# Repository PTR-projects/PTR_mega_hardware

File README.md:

# KPPTR-hardware

Welcome to the KPPTR-hardware repository! This repository contains the design files for the hardware components used in the KPPTR project. The design files have been created using KiCad 6.0, a powerful open-source electronics design automation suite.

## Project Overview

The design files in this repository correspond to the hardware components that make up the KPPTR project, which enhances the capabilities of DIY amateur rockets and high-altitude balloons. The design files have been crafted using KiCad 6.0, a popular and user-friendly tool for creating electronic schematics and PCB layouts. Both hardware and sofware were developed by PTR member!

## Design Files

The repository includes design files for the various hardware components used in the KPPTR project, including:

- **Schematics**: Detailed electronic schematics that illustrate the connections and components used in the design.
- **PCB Layouts**: PCB layout designs that define the placement and routing of components on the printed circuit board.
- **Libraries**: Custom component libraries and footprints used in the project.

## Getting Started

To access and work with the design files, follow these steps:

1. Clone the repository to your local machine.
2. Install [KiCad 9.X](https://www.kicad.org/download/) if you haven't already.
3. Open the KiCad project files (`.pro` files) in the appropriate subdirectories to access the schematics and PCB layouts.

Feel free to explore the design files and customize them to suit your specific needs. If you make any improvements or modifications to the hardware designs, consider contributing back to the repository to help the community.

## Contributors

- [bartekM](https://gitlab.com/space.tech)
- [https://gitlab.com/andrewziebinski](https://gitlab.com/andrewziebinski)
- [https://gitlab.com/Bdabrowsky](https://gitlab.com/Bdabrowsky)
- [https://gitlab.com/krecik1](https://gitlab.com/krecik1)
- [https://gitlab.com/US_air_force](https://gitlab.com/US_air_force)
- [https://gitlab.com/karmelek96](https://gitlab.com/karmelek96)
- and many others!

## License

This project is licensed under the [MIT License](LICENSE). You can freely use, modify, and distribute the code in accordance with the terms of the license.

Unless required by applicable law or agreed to in writing, this
software is distributed on an "AS IS" BASIS, WITHOUT WARRANTIES OR
CONDITIONS OF ANY KIND, either express or implied.

Thank you for your interest in KPPTR-firmware! If you have any questions or feedback, please don't hesitate to reach out to us. Happy coding and safe flights!

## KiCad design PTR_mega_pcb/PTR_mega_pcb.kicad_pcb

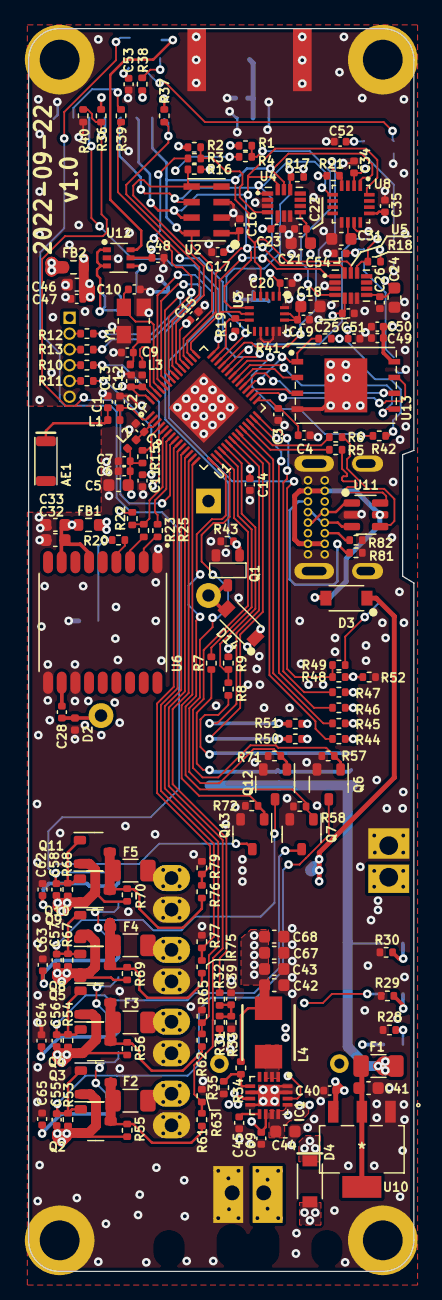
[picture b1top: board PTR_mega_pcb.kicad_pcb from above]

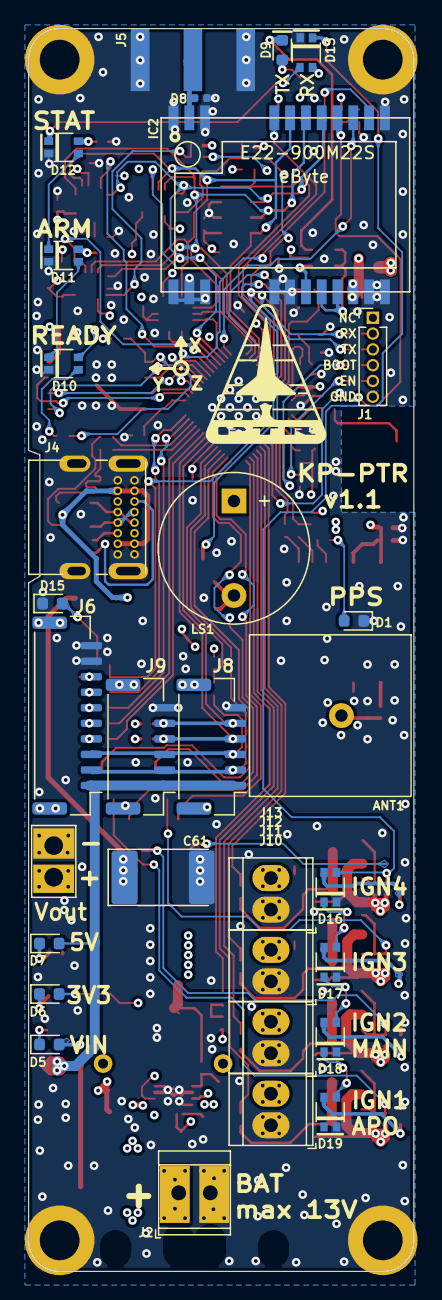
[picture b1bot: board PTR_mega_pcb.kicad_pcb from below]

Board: 4 copper layers, 31.0 x 100.0 mm, 207 parts (32 on the bottom side), 123 nets.

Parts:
AE1: Antenna_Chip; AMCA31-2R450G-S1F-T3
ANT1: APAE1575R1340ABDD6-T; APAE1575 13x13x4mm GPS Patch Antenna
C1: 3.3pF; C_0402_1005Metric
C2: 4.7pF; C_0402_1005Metric
C3, C7, C8, C14, C15, C47, C48: 100n; C_0402_1005Metric
C4, C17, C34, C50, C55, C56, C57, C58: 1uF; C_0402_1005Metric
C5: 10u; C_0603_1608Metric
C6, C11, C13: 1u; C_0402_1005Metric
C9, C10: 12p; C_0402_1005Metric
C12, C39: 10n; C_0402_1005Metric
C16, C19, C20, C22, C23, C25, C26, C35, C49, C51, C52, C53, C54, C62, C63, C64, C65: 100nF; C_0402_1005Metric
C18, C21, C24, C31, C32, C33, C46: 10uF; C_0603_1608Metric
C28: 56pF; C_0402_1005Metric
C40, C69: 100n 50V; C_0402_1005Metric
C41, C42, C43, C67, C68: 10uF 6V3; C_0603_1608Metric
C44: 10uF 16V; C_0603_1608Metric
C45: 470pF; C_0402_1005Metric
C61: 2200uF 16V; CP_EIA-7343-31_Kemet-D
D1, D9: BLUE; LED_0603_1608Metric
D2: DNP; D_0402_1005Metric
D3, D4: D_Schottky; D_SOD-123
D5, D6, D7, D15: GREEN; LED_0603_1608Metric
D8: TBD; D_0402_1005Metric
D10, D11, D12, D13, D16, D17, D18, D19: WS2812B-2020
D14: 1N4148; D_SOD-123
F1, F2, F3, F4, F5: 500mA; Fuse_1206_3216Metric
FB1, FB2: GZ1608D601TF; R_0603_1608Metric
H1, H2, H3, H4: M3; MountingHole_3.2mm_M3_DIN965_Pad
IC1: TPS62140RGTR; QFN50P300X300X100-17N-D
IC2: E22-400M22S; E22-900M22S
J1: ESP32_PROG_CON; PinHeader_1x06_P1.27mm_Vertical
J2, J10, J11, J12, J13: Conn_01x02; TerminalBlock_TE_282834-2_1x02_P2.54mm_Horizontal
J4: USB_C_Receptacle_USB2.0; USB_C_213716
J5: u.fl; SMA_Amphenol_132289_EdgeMount
J6: Conn_01x10_Male; JST_GH_BM10B-GHS-TBT_1x10-1MP_P1.25mm_Vertical
J7: Conn_01x02_Male; TerminalBlock_TE_282834-2_1x02_P2.54mm_Horizontal
J8, J9: Conn_01x06_Male; JST_GH_BM06B-GHS-TBT_1x06-1MP_P1.25mm_Vertical
L1: 1.8nH; L_0402_1005Metric
L2: 3.9nH; L_0402_1005Metric
L3: 24nH; L_0402_1005Metric
L4: MWSA0402S-2R2MT; INDPM4442X200N
LS1: CBT-09427-SMT; Buzzer_12x9.5RM7.6
M1: Reference_frame
Q1, Q6, Q7, Q12, Q13: NMOS_SOT23; SOT-23
Q2, Q3, Q4, Q5, Q8, Q9, Q10, Q11: PMOS_SOT23; SOT-23
R1, R2, R3, R4, R15, R16, R17, R18, R19, R20, R21, R22, R29, R30, R36, R37, R39, R41, R43, R50, R51, R52, R53, R54, R55, R56, R57, R58, R63, R65, R67, R68, R69, R70, R71, R72, R77, R79: 10k; R_0402_1005Metric
R5, R6: 22R; R_0402_1005Metric
R7, R8, R10, R11, R12, R13, R23, R42, R44, R45, R46, R47, R48, R49: 1k; R_0402_1005Metric
R9, R32, R61, R62, R75, R76: 100k; R_0402_1005Metric
R25: 220; R_0402_1005Metric
R28: 22k; R_0402_1005Metric
R31: 100k 1%; R_0402_1005Metric
R33: 10k 1%; R_0402_1005Metric
R34: 470k 1%; R_0402_1005Metric
R35: 150k 1%; R_0402_1005Metric
R38: 2k2; R_0402_1005Metric
R40: DNP; R_0402_1005Metric
R81, R82: 5k1; R_0402_1005Metric
U1: ESP32-S3
U2: MS560702BA03-50; MS5607
U3: H3LIS331; LIS331
U4, U5: LSM6DSO32
U6: L76-L; XCVR_L76-L
U8: MMC5983MA
U10: AZ1117CH-5.0TRG1
U11: USBLC6-2SC6; SOT-23-6
U12: NL27WZU04DBVT1G; SOT-363_SC-70-6
U13: W25Q256; SON127P800X600X80-9N-D
Y1: 7M40000005-40MHz; XTAL_TSX-3225_16.0000MF18X-AC3

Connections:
+3.3VADC: C32.1, C33.1, FB1.2, U6.6 (V_BCKP), U6.8 (VCC)
+3.3VP: C46.1, C47.1, C48.1, FB2.2, IC2.9 (VCC), R36.1, R37.1, R38.1, U12.5 (VCC)
+3V3: C5.1, C6.1, C7.1, C12.1, C13.1, C14.1, C15.1, C16.1, C17.1, C18.1, C19.1, C20.1, C21.1, C22.1, C23.1, C24.1, C25.1, C26.1, C34.1, C35.1, C42.1, C43.1, C49.1, C50.1, C51.1, C52.1, C53.1, C54.1, C62.1, C63.1, C64.1, C65.1, C67.1, C68.1, D6.2 (A), D10.4 (VDD), D11.4 (VDD), D12.4 (VDD), D13.4 (VDD), D14.1 (K), D16.4 (VDD), D17.4 (VDD), D18.4 (VDD), D19.4 (VDD), FB1.1, FB2.1, IC1.7 (FSW), IC1.14 (VOS), J1.1 (3V3), L2.1, L4.2, LS1.1 (+), R1.2, R2.2, R9.2, R15.2, R16.1, R17.1, R18.1, R19.1, R21.1, R22.1, R34.1, R41.1, R50.2, R51.2, U1.20 (VDD3P3_RTC), U1.46 (VDD3P3_CPU), U1.55 (VDDA), U1.56 (VDDA), U2.1 (VDD), U3.1 (VDDIO), U3.14 (VDD), U3.15 (VDDR), U4.5 (VDDIO), U4.8 (VDD), U5.5 (VDDIO), U5.8 (VDD), U8.2 (VDD), U8.13 (VDDIO), U13.8 (VCC)
+5V: D7.2 (A), F1.1, J6.1, J8.1, J9.1
BOOT_PIN: J1.4 (BOOT), R10.2
BUZZER: Q1.1 (G), R43.2, U1.51 (GPIO45)
CHIP_PU: C11.2, R11.1, R15.1, U1.4 (CHIP_PU/RESET)
Earth: C1.2, C2.2, C3.2, C4.2, C5.2, C6.2, C7.2, C8.2, C9.1, C10.2, C11.1, C12.2, C13.2, C14.2, C15.2, C16.2, C17.2, C18.2, C19.2, C20.2, C21.2, C22.2, C23.2, C24.2, C25.2, C26.2, C31.2, C32.2, C33.2, C34.2, C35.2, C39.2, C40.2, C41.2, C42.2, C43.2, C44.2, C45.1, C46.2, C47.2, C48.2, C49.2, C50.2, C51.2, C52.2, C53.2, C54.2, C61.2, C62.2, C63.2, C64.2, C65.2, C67.2, C68.2, C69.2, D1.1 (K), D2.1 (A1), D8.1 (A1), D10.2 (GND), D11.2 (GND), D12.2 (GND), D13.2 (GND), D15.1 (K), D16.2 (GND), D17.2 (GND), D18.2 (GND), D19.2 (GND), H1.1, H2.1, H3.1, H4.1, IC1.6 (AGND), IC1.8 (DEF), IC1.15 (PGND_1), IC1.16 (PGND_2), IC1.17 (EP), IC2.1 (GND), IC2.2 (GND), IC2.3 (GND), IC2.4 (GND), IC2.5 (GND), IC2.10 (GND), IC2.11 (GND), IC2.12 (GND), IC2.20 (GND), IC2.22 (GND), J1.6 (GND), J2.2, J4.A1 (GND), J4.A12 (GND), J4.B1 (GND), J4.B12 (GND), J4.S1 (SHIELD), J5.2 (Ext), J6.9, J6.10, J7.2, J8.6, J9.6, J10.1, J11.1, J12.1, J13.1, Q1.2 (S), Q6.2 (S), Q7.2 (S), Q12.2 (S), Q13.2 (S), R28.2, R29.2, R30.2, R33.2, R35.2, R40.2, R43.1, R52.2, R57.2, R58.2, R63.2, R65.2, R71.2, R72.2, R77.2, R79.2, R81.2, R82.2, U1.57 (GND), U2.2 (PS), U2.3 (GND), U3.5 (GND), U3.10 (GNDR), U3.12 (GND), U3.13 (GND), U3.16 (GND), U4.2 (SDx), U4.3 (SCx), U4.6 (GND), U4.7 (GND), U5.2 (SDx), U5.3 (SCx), U5.6 (GND), U5.7 (GND), U6.1 (GND), U6.10 (GND), U6.12 (GND), U8.9 (GND), U8.11 (GND), U10.1 (ADJ/GND), U11.2 (GND), U12.2 (GND), U13.4 (GND), Y1.2 (GND), Y1.4 (GND)
GPS_IN: R22.2, R23.1, U1.6 (GPIO1/ADC1_CH0)
GPS_OUT: R25.2, U1.7 (GPIO2/ADC1_CH1)
I2C_SCL: J8.4, J9.4, R50.1, U1.22 (GPIO16/ADC2_CH5/XTAL_32K_N)
I2C_SDA: J8.5, J9.5, R51.1, U1.21 (GPIO15/ADC2_CH4/XTAL_32K_P)
IGN1_DET: R61.1, R63.1, U1.12 (GPIO7/ADC1_CH6)
IGN1_EN: Q6.1 (G), R57.1, U1.17 (GPIO12/ADC2_CH1)
IGN2_DET: R62.1, R65.1, U1.11 (GPIO6/ADC1_CH5)
IGN2_EN: Q7.1 (G), R58.1, U1.15 (GPIO10/ADC1_CH9)
IGN3_DET: R75.1, R77.1, U1.10 (GPIO5/ADC1_CH4)
IGN3_EN: Q12.1 (G), R71.1, U1.16 (GPIO11/ADC2_CH0)
IGN4_DET: R76.1, R79.1, U1.9 (GPIO4/ADC1_CH3)
IGN4_EN: Q13.1 (G), R72.1, U1.14 (GPIO9/ADC1_CH8)
IO0: R10.1, U1.5 (GPIO0/BOOT)
IO43: R3.1, R13.1, U1.49 (U0TXD/PROG/GPIO43)
IO44: R4.1, R12.1, U1.50 (U0RXD/PROG/GPIO44)
LED1: R42.2, U1.36 (SPICLK_N/GPIO48)
LSM2_INT: R1.1, R4.2, U5.4 (INT)
LSM_INT: R2.1, R3.2, U4.4 (INT)
unnamed: AE1.1 (FEED), C1.1, L1.1
unnamed: ANT1.1 (A), C28.1, D2.2 (A2)
unnamed: C8.1, L2.2, U1.2 (VDD3P3), U1.3 (VDD3P3)
unnamed: C9.2, L3.2, Y1.1
unnamed: C39.1, R31.2, R32.1, R33.1
unnamed: D1.2 (A), R20.1
unnamed: D5.1 (K), R28.1
unnamed: D6.1 (K), R29.1
unnamed: D7.1 (K), R30.1
unnamed: D8.2 (A2), IC2.21 (ANT), J5.1 (In)
unnamed: D9.2 (A), R38.2
unnamed: D9.1 (K), U12.6 (Y1)
unnamed: D10.3 (DIN), R42.1
unnamed: D10.1 (DOUT), D11.3 (DIN)
unnamed: D11.1 (DOUT), D12.3 (DIN)
unnamed: D12.1 (DOUT), D13.3 (DIN)
unnamed: D13.1 (DOUT), D16.3 (DIN)
unnamed: D14.2 (A), LS1.2 (-), Q1.3 (D)
unnamed: D15.2 (A), R49.1
unnamed: D16.1 (DOUT), D17.3 (DIN)
unnamed: D17.1 (DOUT), D18.3 (DIN)
unnamed: D18.1 (DOUT), D19.3 (DIN)
unnamed: IC1.5 (FB), R34.2, R35.1
unnamed: C45.2, IC1.9 (SS/TR)
unnamed: IC1.1 (SW_1), IC1.2 (SW_2), IC1.3 (SW_3), L4.1
unnamed: IC2.13 (DIO1), R39.1
unnamed: IC2.7 (TXEN), IC2.8 (DIO2), U12.1 (A1), U12.3 (A2)
unnamed: IC2.6 (RXEN), U12.4 (Y2)
unnamed: J1.5 (EN), R11.2
unnamed: J4.A5 (CC1), R81.1
unnamed: J4.B5 (CC2), R82.1
unnamed: J4.A6 (D+), J4.B6 (D+), U11.3 (I/O2)
unnamed: J4.A7 (D-), J4.B7 (D-), U11.1 (I/O1)
unnamed: J6.4, R44.1
unnamed: J6.5, R45.1
unnamed: J6.6, R46.1
unnamed: J6.7, R47.1
unnamed: J6.8, R48.1, R52.1
unnamed: F2.2, J10.2
unnamed: F3.2, J11.2
unnamed: F4.2, J12.2
unnamed: F5.2, J13.2
unnamed: F2.1, Q2.3 (D), Q3.3 (D), R55.2, R61.2
unnamed: C55.2, Q2.1 (G), Q3.1 (G), Q6.3 (D), R53.2
unnamed: F3.1, Q4.3 (D), Q5.3 (D), R56.2, R62.2
unnamed: C56.2, Q4.1 (G), Q5.1 (G), Q7.3 (D), R54.2
unnamed: F4.1, Q8.3 (D), Q9.3 (D), R69.2, R75.2
unnamed: F5.1, Q10.3 (D), Q11.3 (D), R70.2, R76.2
unnamed: C58.2, Q10.1 (G), Q11.1 (G), Q13.3 (D), R68.2
unnamed: C57.2, Q8.1 (G), Q9.1 (G), Q12.3 (D), R67.2
unnamed: R7.1, U1.18 (GPIO13/ADC2_CH2)
unnamed: R8.1, R9.1, U1.19 (GPIO14/ADC2_CH3)
unnamed: R5.2, U1.25 (GPIO19/USB_D-/ADC2_CH8)
unnamed: R6.2, U1.26 (GPIO20/USB_D+/ADC2_CH9)
unnamed: C2.1, L1.2, U1.1 (LNA_IN/RF)
unnamed: C3.1, C4.1, U1.29 (VDD_SPI)
unnamed: C10.1, U1.53 (XTAL_N), Y1.3 (2)
unnamed: L3.1, U1.54 (XTAL_P)
unnamed: R20.2, U6.4 (1PPS)
unnamed: C28.2, U6.11 (RF_IN)
unnamed: R23.2, U6.3 (RXD1)
unnamed: R25.1, U6.2 (TXD1)
unnamed: C31.1, U8.10 (CAP)
unnamed: C41.1, F1.2, U10.2 (OUTPUT), U10.4 (EPAD)
RF_BUSY: IC2.14 (BUSY), U1.42 (GPIO37)
RF_DIO1: R39.2, U1.37 (SPICLK_P/GPIO47)
RF_RST: IC2.15 (NRST), R36.2, R40.1, U1.8 (GPIO3/ADC1_CH2)
SERVO_1: R44.2, U1.23 (GPIO17/ADC2_CH6/DAC_2)
SERVO_2: R45.2, U1.24 (GPIO18/ADC2_CH7/DAC_1)
SERVO_3: R46.2, U1.27 (GPIO21)
SERVO_4: R47.2, U1.28 (SPI_CS1/GPIO26)
SERVO_EN: R48.2, R49.2, U1.52 (GPIO46)
SPI0_CLK: U1.33 (SPICLK/GPIO30), U13.6 (CLK)
SPI0_CS: R41.2, U1.32 (SPICS0/GPIO29), U13.1 (~CS)
SPI0_DI: U1.35 (SPID/GPIO32), U13.5 (DI(IO0))
SPI0_DO: U1.34 (SPIQ/GPIO31), U13.2 (DO(IO1))
SPI0_HOLD: U1.30 (SPIHD/GPIO27), U13.7 (IO3)
SPI0_WP: U1.31 (SPIWP/GPIO28), U13.3 (IO2)
SPI_CLK: IC2.18 (SCK), U1.45 (MTDO/JTAG/GPIO40), U2.8 (SCLK), U3.4 (SCL/SPC), U4.13 (SCL/SCK), U5.13 (SCL/SCK), U8.1 (SCL/SPI_SCK)
SPI_CS_LIS: R19.2, U1.41 (GPIO36), U3.8 (CS)
SPI_CS_LORA: IC2.19 (NSS), R37.2, U1.48 (MTMS/JTAG/GPIO42)
SPI_CS_LSM: R17.2, U1.40 (GPIO35), U4.12 (CS)
SPI_CS_LSM2: R18.2, U1.38 (GPIO33), U5.12 (CS)
SPI_CS_MAG: R21.2, U1.39 (GPIO34), U8.4 (~SPI_CS)
SPI_CS_MS5607: R16.2, U1.47 (MTDI/JTAG/GPIO41), U2.4 (~CSB), U2.5 (~CSB)
SPI_MISO: IC2.16 (MISO), U1.43 (GPIO38), U2.6 (SDO), U3.7 (SA0/SDO), U4.1 (MISO/SA0), U5.1 (MISO/SA0), U8.5 (SPI_SDO)
SPI_MOSI: IC2.17 (MOSI), U1.44 (MTCK/JTAG/GPIO39), U2.7 (SDI/SDA), U3.6 (SDA/SDI), U4.14 (SDA/MOSI), U5.14 (SDA/MOSI), U8.16 (SDA/SPI_SDI)
U0RXD: J1.2 (RX0), R12.2
U0TXD: J1.3 (TX0), R13.2
UART1_IN: J6.3, J8.3, J9.3, R8.2
UART1_OUT: J6.2, J8.2, J9.2, R7.2
USB_DM: R5.1, U11.6 (I/O1)
USB_DP: R6.1, U11.4 (I/O2)
VBAT_MEAS: R32.2, U1.13 (GPIO8/ADC1_CH7)
VBUS: D3.2 (A), J4.A4 (VBUS), J4.A9 (VBUS), J4.B4 (VBUS), J4.B9 (VBUS), U11.5 (VBUS)
VCC: C40.1, C55.1, C56.1, C57.1, C58.1, D4.2 (A), J2.1, J7.1, Q2.2 (S), Q3.2 (S), Q4.2 (S), Q5.2 (S), Q8.2 (S), Q9.2 (S), Q10.2 (S), Q11.2 (S), R31.1, R53.1, R54.1, R55.1, R56.1, R67.1, R68.1, R69.1, R70.1, U10.3 (INPUT)
VDD: C44.1, C61.1, C69.1, D3.1 (K), D4.1 (K), D5.2 (A), IC1.10 (AVIN), IC1.11 (PVIN_1), IC1.12 (PVIN_2), IC1.13 (EN)

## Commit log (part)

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2022-02-06 Configure SAST in `.gitlab-ci.yml`, creating this file if it does not already exist
2022-02-07 KiCad libs created
    - ublox GNSS receivers added
    - MS5607 added
    - LIS331 - symbol added
    - ESP32-S3 - symbol added
    - USB C added
    - LSM6DSO32 - symbol added
2022-02-07 Added:
    - LIS331 footprint
    - LSM6DSO32 footprint
    - ESP32-S3FN8 footprint
2022-02-07 .gitignore added
2022-02-09 Small schematic update
    Added 3.2x2.5mm crystal (symbol + footprint)
2022-02-09 Small schematic update
2022-02-20 LIS + SDCARD Signed-off-by: kretu <krecik@gmail.com>
2022-02-20 poprawiony babol przy sd Signed-off-by: kretu <krecik@gmail.com>
2022-02-20 SD bez pullupa na CLK jak w gotowym układzie od ST
2022-02-20 Dodane IMU
2022-02-20 Kondensatory przy IMU zgodnie z DS których nie było u Adafruit
2022-02-22 IGN & PSU added
2022-02-28 LSM6DSO32 added
2022-03-04 Magnetometr Buzzer 3xLED Signed-off-by: kretu <krecik@gmail.com>
2022-03-05 GPS lora wrzucone symbole Signed-off-by: kretu <krecik@gmail.com>
2022-03-07 GPS Signed-off-by: kretu <krecik@gmail.com>
2022-03-08 Footprints IN IMU9DOF OUT Signed-off-by: kretu <krecik@gmail.com>
2022-03-09 First sight of pcb Signed-off-by: kretu <krecik@gmail.com>
2022-03-09 Small changes before sleep Signed-off-by: kretu <krecik@gmail.com>
2022-03-11 Golaiath fight with board Signed-off-by: kretu <krecik@gmail.com>
2022-03-14 RF added, multiple small changes
2022-04-27 Weryfikacja footprintow faza I Signed-off-by: kretu <krecik@gmail.com>
2022-04-27 Footprinty drobnicy
2022-05-07 Removed SD card
    Added Flash
2022-05-07 Ogarnięty GPS i RF do anteny
2022-05-07 Kilka zmian.
    -dodany tranzystor P/N mosfet do biblioteki i zapalników
    -dodany komentarz o impedancji ścieżek RF
2022-05-09 Szlifowanie schematu
2022-06-01 Update po spotkaniu
2022-06-02 Footprint mosfeta
2022-06-02 Grupowanie
2022-06-03 1 proba zmieszczenia wszystkiego
2022-06-03 1 próba pomieszczenia wszystkiego
2022-06-03 Add some missing 3D models
2022-06-04 swiatelko w tunelu aby zmiescic wszystko
2022-06-11 chyba wszystkie footprinty
2022-06-11 PCB update
2022-06-12 PCB update 2
2022-06-25 SCH&PCB update
2022-06-25 Next PCB update
    -fixes
    -logos added
2022-06-25 Modele 3d uzupelnione i minimalnie poprawione opisy
2022-06-26 PCB small update
2022-06-26 Footprints and PCB update
2022-06-26 PCB finished
    Gerbers prepared
2022-06-27 PCB update
    Teardrops added
2022-08-06 PCB update to v1.0
2022-09-06 Work in progress
2022-09-07 Second LSM added
    Both LSM has INT connected
    Small pins changes
2022-09-07 IGN detector update
2022-09-07 JLC codes added
2022-09-08 Igniters rework
2022-09-09 Igniters rework v2
2022-09-12 brakujące footprinty
2022-09-12 Flash footprint updated
    Overlay cleaning
2022-09-14 DC-DC added
    multiple PCB changes
2022-09-15 One step closer to perfection!
2022-09-15 Parts renumbered! Noice!
2022-09-19 Backup capacitor changed from electro to tantal.
    Multiple kung fu changes
2022-09-19 SW removed, tantal added, powerplane rework
2022-09-23 Wersja produkcyjna v1
2022-09-26 Release v0.1
2022-11-18 Release v1
2023-08-13 README and LICENSE update
2023-12-17 New schematic revision v1.1:
    - added 'DNP' info for few components
    - some stylistic improvements
    - added comment about I2C pins glitch
2025-06-22 + Kicad update to 9.0
    + CC resistors added
2025-06-25 - Removed old teardrops polygons
    - Removed unused LDO
    - Removed unused LNA
    + DC-DC with additional capacitors
    + IGN connectors moved closer together
    - removed additional unused resistors for igniter detection
    + small rearrangement of DC-DC etc
